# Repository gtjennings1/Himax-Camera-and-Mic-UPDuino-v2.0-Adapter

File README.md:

# Himax-Camera-and-Mic-UPDuino-v2.0-Adapter

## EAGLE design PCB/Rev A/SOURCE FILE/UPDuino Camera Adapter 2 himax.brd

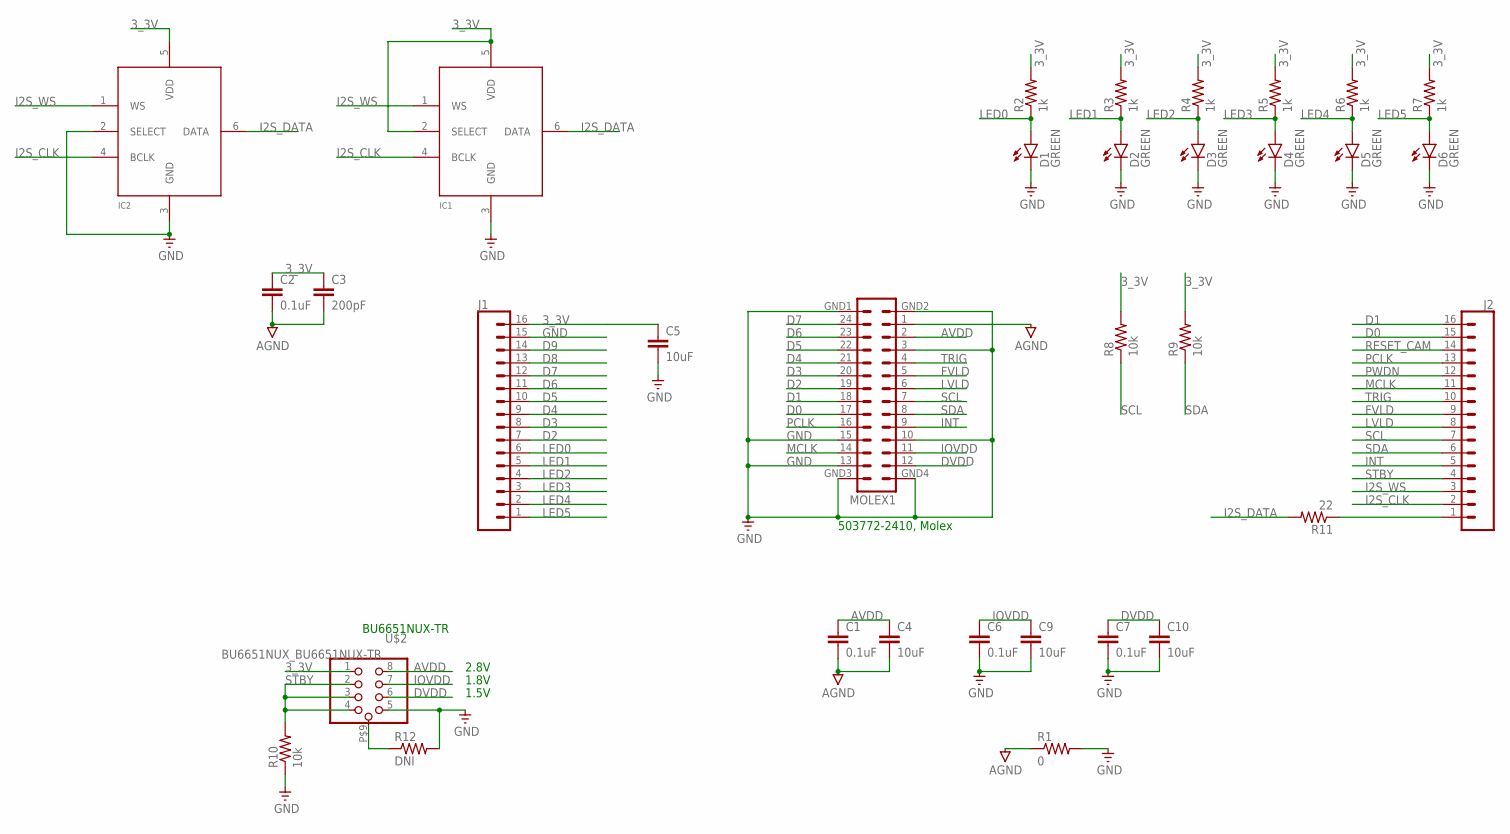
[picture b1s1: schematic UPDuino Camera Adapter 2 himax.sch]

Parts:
C1, C2, C6, C7: 0.1uF; 0603
C3: 200pF; 0603
C4, C5, C9, C10: 10uF; 0603
D1, D2, D3, D4, D5, D6: GREEN; LED-0603
IC1, IC2: MIC_I2S_SPH0645; SPH0645LM4H
J1, J2: CONN_16; 1X16
MOLEX1: MOLEX-5037722410_MOLEX
R1: 0; 0603-RES
R2, R3, R4, R5, R6, R7: 1k; 0603-RES
R8, R9, R10: 10k; 0603-RES
R11: 22; 0603-RES
R12: DNI; 0603-RES
U$2: BU6651NUX_BU6651NUX-TR

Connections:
3_3V: C2.1, C3.1, C5.1, IC1.2 (SELECT), IC1.5 (VDD), IC2.5 (VDD), J1.16, R2.2, R3.2, R4.2, R5.2, R6.2, R7.2, R8.2, R9.2, U$2.1 (8)
AGND: C1.2, C2.2, C3.2, C4.2, MOLEX1.1, R1.1
AVDD: C1.1, C4.1, MOLEX1.2, U$2.8 (1)
D0: J2.15, MOLEX1.17
D1: J2.16, MOLEX1.18
D2: J1.7, MOLEX1.19
D3: J1.8, MOLEX1.20
D4: J1.9, MOLEX1.21
D5: J1.10, MOLEX1.22
D6: J1.11, MOLEX1.23
D7: J1.12, MOLEX1.24
D8: J1.13
D9: J1.14
DVDD: C7.1, C10.1, MOLEX1.12, U$2.6 (3)
FVLD: J2.9, MOLEX1.5
GND: C5.2, C6.2, C7.2, C9.2, C10.2, D1.C, D2.C, D3.C, D4.C, D5.C, D6.C, IC1.3 (GND), IC2.2 (SELECT), IC2.3 (GND), J1.15, MOLEX1.3, MOLEX1.10, MOLEX1.13, MOLEX1.15, MOLEX1.GND1, MOLEX1.GND2, MOLEX1.GND3, MOLEX1.GND4, R1.2, R10.1, R12.2, U$2.5 (4)
I2S_CLK: IC1.4 (BCLK), IC2.4 (BCLK), J2.2
I2S_DATA: IC1.6 (DATA), IC2.6 (DATA), R11.2
I2S_WS: IC1.1 (WS), IC2.1 (WS), J2.3
INT: J2.5, MOLEX1.9
IOVDD: C6.1, C9.1, MOLEX1.11, U$2.7 (2)
LED0: D1.A, J1.6, R2.1
LED1: D2.A, J1.5, R3.1
LED2: D3.A, J1.4, R4.1
LED3: D4.A, J1.3, R5.1
LED4: D5.A, J1.2, R6.1
LED5: D6.A, J1.1, R7.1
LVLD: J2.8, MOLEX1.6
MCLK: J2.11, MOLEX1.14
unnamed: J2.1, R11.1
unnamed: R12.1, U$2.P$9 (9)
PCLK: J2.13, MOLEX1.16
PWDN: J2.12
RESET_CAM: J2.14
SCL: J2.7, MOLEX1.7, R8.1
SDA: J2.6, MOLEX1.8, R9.1
STBY: J2.4, R10.2, U$2.2 (7), U$2.3 (6), U$2.4 (5)
TRIG: J2.10, MOLEX1.4

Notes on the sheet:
BU6651NUX-TR
503772-2410, Molex
1.8V
1.5V
2.8V

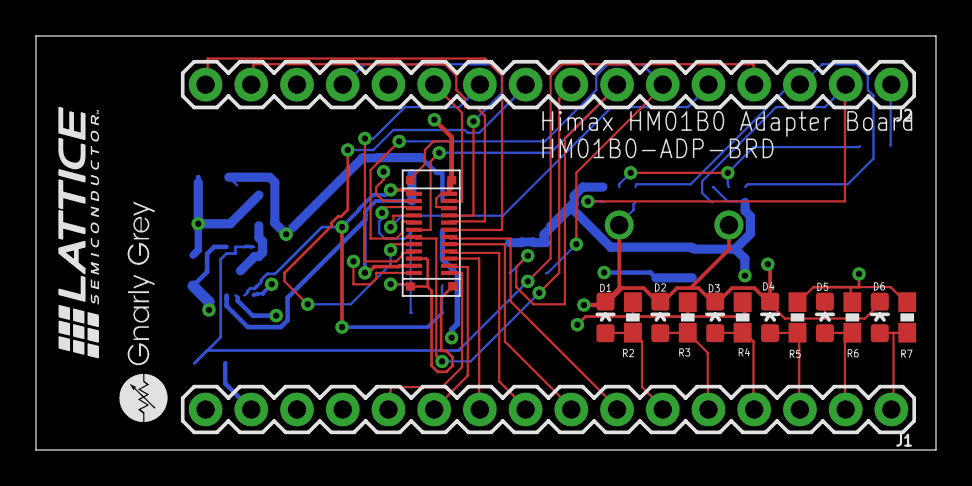
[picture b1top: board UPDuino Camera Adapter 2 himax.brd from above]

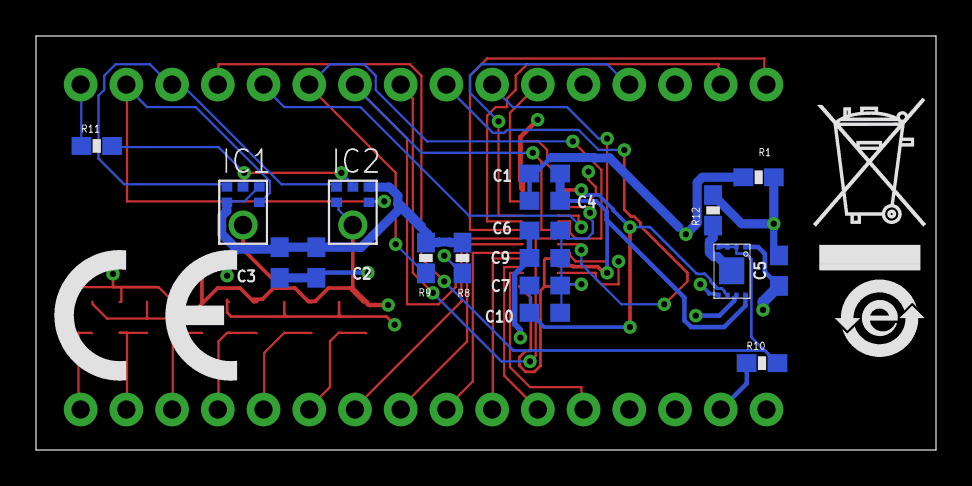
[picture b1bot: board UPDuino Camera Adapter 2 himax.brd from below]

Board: 4 copper layers, 50.0 x 23.0 mm, 33 parts (18 on the bottom side), 34 nets.

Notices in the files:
parts and their libraries:
SparkFun-Capacitors: Licensing: Creative Commons ShareAlike 4.0 International - https://creativecommons.org/licenses/by-sa/4.0
microbuilder: This work is placed in the public domain, and may be freely used for commercial and non-commercial work with the following conditions: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
